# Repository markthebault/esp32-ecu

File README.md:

# ESP32 ECU

A home-solderable ESP32-S3 bench monitor and engine-control development platform. The project combines a compact through-hole carrier, ECU Studio in the browser, ESP-NOW screen telemetry, and a shared C++ fuel/spark core exercised with software engine models.

> **Current status: verified software/bench checkpoint.** Feature expansion is paused. All normal physical engine outputs remain inhibited. This is not yet a complete ECU that can run an engine or replace Speeduino.

[Checkpoint and evidence](docs/bench-checkpoint.md) · [Feature coverage](docs/engine-feature-coverage.md) · [Setup guide](docs/web-configuration.md) · [Latest hardware draft](hardware/a7-boost-interface/README.md) · [Tuning compatibility](tuning/README.md)

*A7 CAD draft, not a photograph or fabrication release. Some components use simplified envelopes or have no body model. The raised ESP32 module, header spacing, inward antenna reservation and enclosure fit remain provisional.*

## What it does today

| Area | Implemented capabilities | Current scope |
| --- | --- | --- |
| Sensor monitoring | Six protected analog inputs plus battery and 5 V rail measurement; linear, lookup-table and NTC conversions, 55 kΩ input-loading compensation and optional ratiometric calibration | Firmware and browser paths implemented; actual electrical behavior still needs measurement |
| Configuration | Persistent sensor profiles and engine tunes, import/export, strict validation, schema migration, stale-revision rejection and storage-fault reporting | Same parser/conversion code on target and host; defaults are uncalibrated |
| Crank and cam | Generic missing-tooth decoder, protected Hall interfaces, sync diagnostics and 720° sequential phase handling with cam-loss cuts | Firmware plus generated 60-2/cam events in simulation; target timing unmeasured |
| Fuel and spark | 1–8 virtual even-fire cylinders; batch/wasted, semi-sequential and sequential strategies; 16 × 16 fuel/spark/lambda maps and individual cylinder trims | Shadow calculations and software-in-the-loop (SIL), with physical outputs inhibited |
| Corrections and control | Cranking, warmup/afterstart, acceleration/deceleration, battery/dead-time/dwell compensation, rev limiting, overrun cut and bounded lambda PI; idle, boost/overboost, flex and secondary-table development | Implemented development paths with configuration and diagnostics; no physical actuator acceptance |
| Debugging | Raw ADC/rail/interlock status, listen-only CAN counters, bounded tooth/timing traces and engine logs, source/age/loss labels, JSON and MSL exports | Host checks pass; physical capture integrity and runtime load remain open |
| Paired screens | Authenticated read-only ESP-NOW sensor/engine telemetry; button or UI pairing, candidate approval and persisted unpair | ECU side implemented; screen firmware and real two-device RF tests remain open |
| Tuning tools | Own012 TunerStudio definition and offline MSQ editing; MegaLogViewer HD opens and plots current MSL files | Actual application/file workflows checked; supported online TunerStudio integration is unresolved |

**Shadow** means the ESP32 calculates proposed commands without driving engine outputs. **SIL** means the native C++ ECU receives synthetic sensor/tooth events and drives virtual outputs into a software plant. Neither establishes physical engine operation. The [full coverage matrix](docs/engine-feature-coverage.md) records the details and evidence for each feature.

## ECU Studio and test screenshots

The same local UI runs on the ESP32 service AP and the desktop simulator. These fresh Chrome captures use **synthetic host data**, with no hardware connected. The calibration curve is an unconfirmed example; the engine settings are illustrative defaults.

| Sensor calibration | Engine configuration and diagnostics |
| --- | --- |
|  |  |
| Signal conversion, input diagnosis and connector guidance | Four-cylinder default profile after a completed virtual run |

| Browser-driven engine test | Screen management |
| --- | --- |
|  |  |
| Actual **Run 12 virtual seconds** action, using the unvalidated reduced-order plant | Pair, approve and remove a synthetic screen; no RF packets transmitted |

[Capture sources, checks and image hashes](docs/images/readme/provenance.json) accompany the images. The requested LED policy is steady green normally, blinking blue while pairing and blinking red for detected problems, with faults taking priority. Browser tests verify the requested states, not physical light output. See [pairing, buttons and telemetry](docs/espnow.md).

## Hardware and revision status

- **Carrier:** 120 × 120 mm, six layers, through-hole assembly with ordinary leaded parts and directly soldered DIP devices. The ESP32 remains pluggable.
- **Selected module:** 44-pin Type-C **ESP32-S3 N16R8**, with 16 MB flash and 8 MB PSRAM. The [supplied listing PDF](hardware/references/esp32-s3-44pin-aliexpress.pdf) is preserved in the repository. Actual module/socket dimensions still need confirmation.
- **Fitted engine capacity:** four injector and four smart-coil command channels. Virtual cylinders 5–8 have no fitted drivers. There is no dumb-coil power stage or raw wideband-sensor controller.
- **Mechanical work:** printable screw-mounted enclosure sources, gasket concept and sealed PAIR/RESET button wiring are retained. Later module, antenna, harness and accessory changes still need physical fit checks.

| Revision | Where to look | Status |
| --- | --- | --- |
| A7 carrier + isolated idle/boost accessories | [Carrier CAD and BOM](hardware/a7-boost-interface/README.md), [shared harness and electrical work](docs/engine-boost-hardware.md) | Latest development draft; boost GPIO allocation remains inactive; no fabrication release |
| A6 flex/RGB and A5 idle work | [A6 layout](docs/engine-a6-layout.md), [idle isolation](docs/engine-idle-isolation.md) | Preserved development drafts with electrical/assembly holds |
| A3 board, manufacturing files and case | [Archived hardware](hardware/a3-compact/), [Gerbers/drills](manufacturing/a3/), [enclosure](enclosure/a3/) | Historical package; do not apply its wiring or fit assumptions to A7 |

## What it does not do

- **Run a physical engine.** The normal images keep engine commands and ARM inhibited. Injector flow/flyback, coil behavior, target timing, watchdog/reset behavior and loaded supply performance remain unqualified.
- **Provide the full Speeduino feature set.** Other OEM trigger decoders, raw VR conditioning, VVT, knock processing, staged injection, launch/flat shift/nitrous, stepper idle and autotune are missing. DBW and OEM CAN/immobilizer integration remain outside the current bench scope.
- **Offer supported online TunerStudio tuning.** The transport and offline file paths exist; online application acceptance is still unresolved. Offline MSQ and MegaLogViewer file compatibility do not prove a physical USB connection.
- **Establish engine-model equivalence or a usable calibration.** Comparisons execute pinned production Speeduino code, but retained reference runs still fail finite-step convergence checks. The plants are uncalibrated research models, and no engine has been tested.
- **Establish vehicle or enclosure qualification.** Physical RF/range, surge/EMI, thermal, current capacity, splash resistance and printed fit remain untested. CAD/ERC/DRC and passing software tests do not establish those properties.

## Work in progress and open items

Feature expansion is **paused at the verified checkpoint**, rather than complete. These are the remaining work areas when development resumes:

| Work area | Remaining work |
| --- | --- |
| Hardware release | Measure the real N16R8/socket/antenna geometry; resolve A7 and accessory electrical, exact-part, harness and enclosure holds before releasing matching fabrication files |
| Bench and HIL testing | Instrument real timing, ADC/supply behavior, interlocks, reset/watchdog recovery, dummy-load outputs and two-device ESP-NOW; then assess physical/environmental limits separately |
| Simulator comparison | Resolve failed reference refinements and matched turbo/map assumptions; preserve causal tests and numerical checks instead of treating a plausible RPM trace as acceptance |
| External tools and screens | Resolve online TunerStudio compatibility and physical USB checks; implement and test a separate screen receiver against the authenticated telemetry protocol |
| Broader ECU coverage | Add missing decoders and control features together with their hardware, UI, configuration, diagnostics and fault tests |

[Engine comparison and remaining convergence failures](docs/engine-shaft-integration.md) · [Current tuning evidence](docs/engine-tuning-application.md) · [Target timing limits](docs/engine-target-timing.md)

## Try the desktop UI or build firmware

The host needs Python 3, a C/C++ compiler and the pinned PlatformIO ESP-IDF package for its cJSON bridge. Follow the [setup guide](docs/web-configuration.md) for dependencies and bench wiring. Use a new output/state directory and a free port:

```sh
# Selected-module bench image. This does not flash a device.
python3 scripts/build_firmware_preserved.py \
  --environment compact_n16r8_web \
  --output .cache/engine/NEW-WEB-BUILD

# Same UI, synthetic measurements, no hardware connection.
python3 tools/web_server.py \
  --port 8765 --state .cache/engine/NEW-PREVIEW/profile.json
```

Open **http://127.0.0.1:8765**. On the actual device, service AP access requires J3 open at startup and a fresh per-boot password read from UART. The [guide](docs/web-configuration.md) covers power isolation and flashing. `compact_n16r8_flex_dev` requires its matching development wiring; `compact_a3_web` belongs to historical A3 hardware.

## What has been verified

The [checkpoint record](reports/engine/bench-checkpoint/README.md) contains the full native ASan/UBSan suite, **99 host/API/config/protocol checks**, sensor-storage fault tests, **four Chrome workflows** and **three fresh inhibited firmware builds**, with source/build hashes and independent review. No device was flashed. For this README, calibration, profile/logging and pairing browser checks were rerun successfully, followed by the captured four-cylinder SIL/UI workflow above.

The verified scope is software and declared bench paths. Physical hardware, RF, fit and engine operation remain open.

<details>
<summary>Historical A3 build package and earlier revisions</summary>

The original deliverables remain available for their original revision:

[Grouped BOM](hardware/a3-compact/BOM.md) · [Shopping CSV](hardware/a3-compact/bom-shopping.csv) · [KiCad project](hardware/a3-compact/esp32-ecu.kicad_pro) · [26-page manual](output/pdf/esp32-ecu-a3-build-calibration-debug-manual.pdf) · [Print files](enclosure/a3/) · [Complete A3 ZIP](build/esp32-ecu-a3-120-web-manual-case.zip)

[A3 native CAD checks](reports/a3/validation-summary.json) and [CAD enclosure-fit report](enclosure/a3/fit-check.json) are historical software/CAD evidence. They do not qualify a printed assembly or later hardware. Exact passive parts and some fit-dependent purchases remain flagged in the BOM.

[Revision history](docs/history.md) · [Original compact-board notes](docs/compact.md)

</details>

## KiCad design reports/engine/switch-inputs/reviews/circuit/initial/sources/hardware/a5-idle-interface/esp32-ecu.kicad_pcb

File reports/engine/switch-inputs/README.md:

# Guarded switch inputs: development checkpoint

Target firmware now acquires the two SW2-J4-DRAFT1 contacts, binds coherent source-tagged samples into the controller, latches faults across skipped control observations and exposes bus/wiring diagnostics in the UI. Defaults make no I2C device requests. Source timestamps, readback/challenge checks, measured acceptance budgets and requalification are explicit. Selected web-build engine outputs remain inhibited.

The separate80x60mm THT accessory has a native schematic/routed PCB, candidate BOM, incompatible internal/contact connectors and a reviewed ground-return pour. **HOLD: no fabrication, physical engine, electrical/environmental, thermal or enclosure-fit qualification.** The expander selftest cannot qualify an analog conditioner or prove two-wire continuity. Fresh secondary-enabled coupled engine acceptance remains open.

- [Current hardware/wiring/debug guide](../../../hardware/switch-inputs/README.md)
- [Source bindings](source-bindings.json), [checks](checks.json) and [artifact manifest](artifact-manifest.json)
- [Independent software assessment](reviews/software/assessment.txt) and [review](reviews/software/review.json):12,278 assertions, including actual engine/switch services, skipped observations, reset/budget/fault races and UI provenance.
- [Independent architecture assessment](reviews/architecture/assessment.txt). The circuit review packet is under `reviews/circuit/`, with its own source bindings, manifest and standalone replay.
- [Native schematic](validation/cad/schematic.svg), [copper](validation/cad/copper.svg), [reference locator](validation/reference-locator/assembly.svg). The locator uses an annotation-only export copy; all serialized non-reference tokens and geometry match the unchanged production PCB. It is not a fit/assembly qualification.
- [Circuit results](validation/circuit/results.json):95 conditional ngspice cases and retained custom decks/vectors. Generic transistor/diode/clamp/supervisor assumptions are not manufacturer models. Bus-feed and carrier3V3-feed currents are separate. Steady18V experiments are not input ratings or automotive surge tests.
- Native/full existing Python tests, three additional stale-binding tests, eight installed-Chrome workflows and three Linux target builds passed. Static output-policy/ISR/USB audits do not establish actual timing, heap, stack or physical behavior.

The immutable software review copied the earlier secondary feature guide as context. The sole declared difference is the updated guide describing this implemented path and its prototype/physical gates; accepted software remains byte-identical. Original local review manifests are retained. Their publication projections explicitly list omitted manufacturer document/page copies and compiled executables/objects. The full local research cache remains intact. The circuit review has a separate standalone publication manifest.

Verification is archival by default. Later project changes do not rewrite this checkpoint. From the repository root:

```sh
python3 tools/verify_switch_inputs_evidence.py
python3 tools/verify_switch_inputs_evidence.py --check-live-sources
uv run --with numpy python tools/verify_switch_inputs_evidence.py --replay --ngspice .cache/tools/ngspice-package/payload/usr/bin/ngspice
```

Replay rebuilds frozen portable/actual-service independent probes in a temporary directory. The optional circuit replay requires the recorded ngspice binary and compares all95 result rows. Native KiCad/target builds and hardware measurements are separate operations. Nothing was flashed and no vendor message was sent.

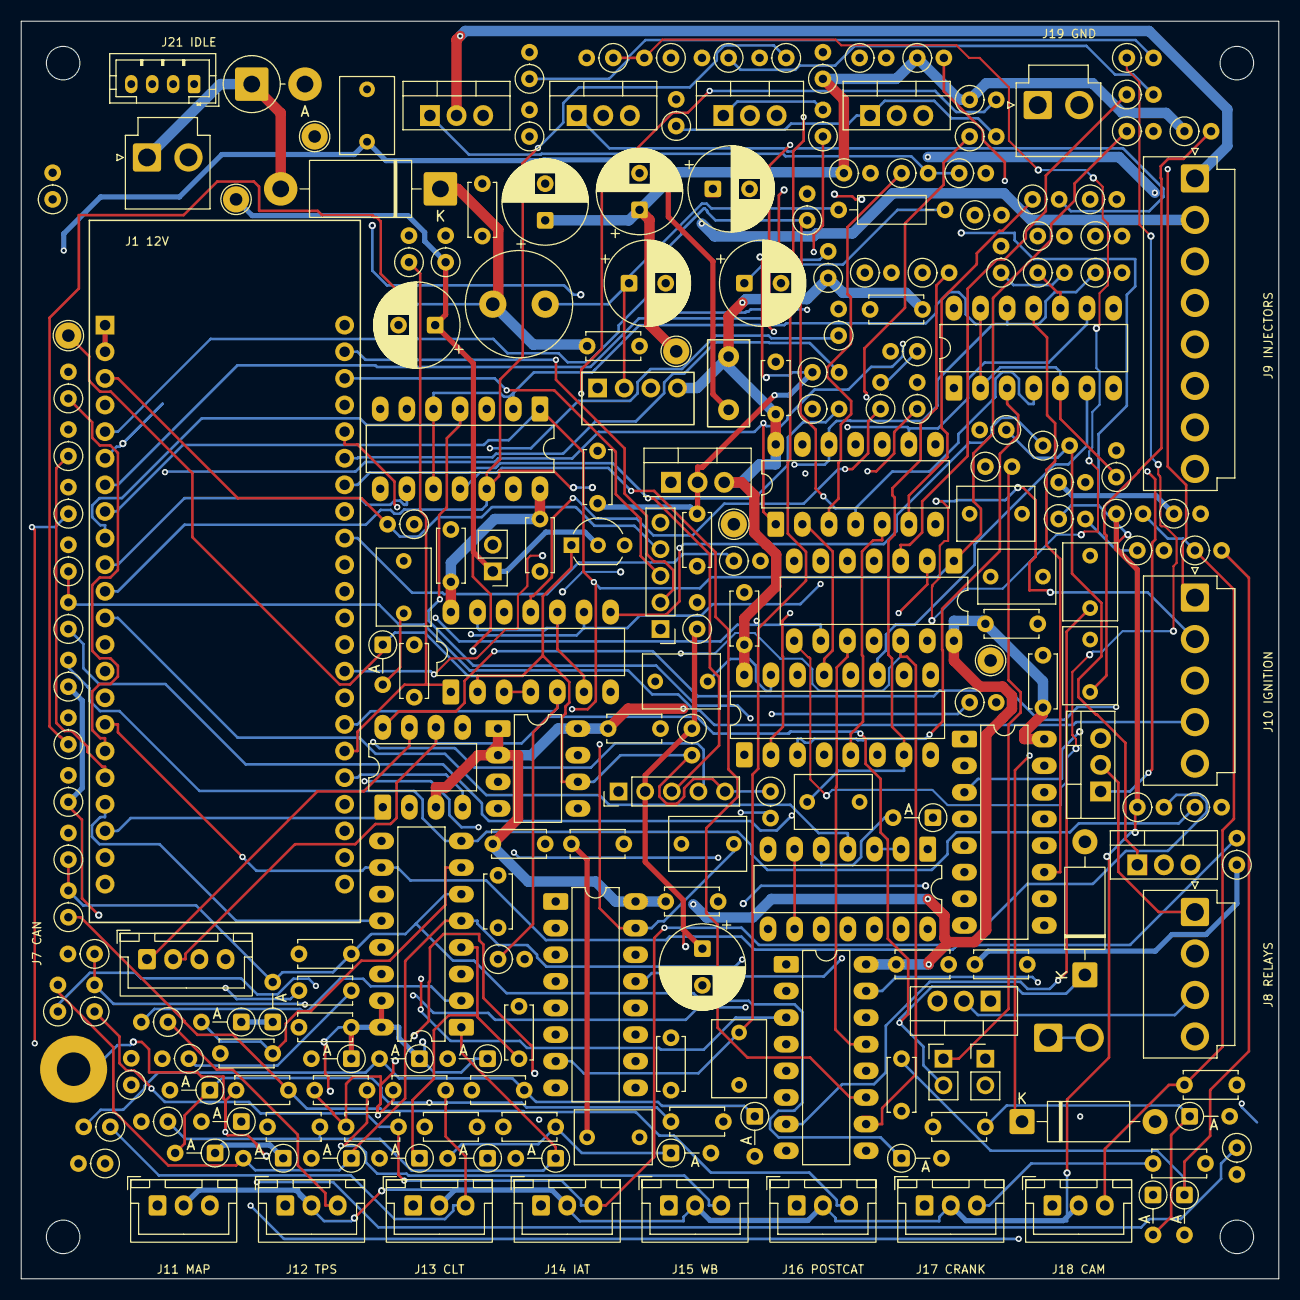
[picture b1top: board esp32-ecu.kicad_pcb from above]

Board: 6 copper layers, 120.0 x 120.0 mm, 221 parts (0 on the bottom side), 119 nets.

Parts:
C1, C2, C45: 47u 63V; CP_Radial_D8.0mm_P3.50mm
C3, C46: 100n 100V; C_Disc_D5.0mm_W2.5mm_P5.00mm
C5, C6: 22u 16V electrolytic; CP_Radial_D8.0mm_P3.50mm
C9: 22u 10V ESR 0.3-1R; CP_Radial_D8.0mm_P3.50mm
C10, C14, C15, C16, C28, C32, C33, C34, C35, C36, C37, C38, C39, C40, C41, C42, C43: 100n; C_Disc_D5.0mm_W2.5mm_P5.00mm
C11, C12, C29: 1u; C_Rect_L7.2mm_W5.0mm_P5.00mm
C13: 10u; CP_Radial_D8.0mm_P3.50mm
C20, C21, C22, C23, C24, C25, C26, C27: 10n; C_Disc_D5.0mm_W2.5mm_P5.00mm
C30, C31: 100p C0G; C_Disc_D5.0mm_W2.5mm_P5.00mm
C47: 4.7n 100V; C_Disc_D5.0mm_W2.5mm_P5.00mm
C61, C62, C63, C64: 270n 5% FILM; C_Rect_L7.2mm_W5.0mm_P5.00mm
C81, C82, C83, C84: 68n 5% FILM; C_Rect_L7.2mm_W5.0mm_P5.00mm
C150, C151, C152, C153, C154, C155: 1n C0G 100V; C_Disc_D5.0mm_W2.5mm_P5.00mm
C156, C157: 100p C0G 100V; C_Disc_D5.0mm_W2.5mm_P5.00mm
D1: 1.5KE27CA; D_DO-201AD_P5.08mm_Vertical_AnodeUp
D2: SB5100; D_DO-201AD_P15.24mm_Horizontal
D3, D100, D101, D110, D111, D120, D121, D130, D131, D140, D141, D150, D151, D160, D161, D170, D171, D200, D201, D210, D211: BAT85; D_DO-35_SOD27_P3.81mm_Vertical_AnodeUp
D22, D23: P6KE24CA; D_DO-15_P12.70mm_Horizontal
F2: PTC 100mA radial; PTC_MF_R010
H1, H2, H3, H4: M3 NPTH; MountingHole_3.2mm_M3
H5: M3 SHIELD LUG; MountingHole_3.2mm_M3_Pad
J1: FUSED_KEY_12V; JST_VH_B2P-VH_1x02_P3.96mm_Vertical
J2: UART_FLASH_3V3_ONLY; PinHeader_1x05_P2.54mm_Vertical
J3: NORMALLY_OPEN_INTERLOCK; PinHeader_1x02_P2.54mm_Vertical
J4: EXPANSION_3V3; PinHeader_1x05_P2.54mm_Vertical
J7: CAN_H_L_G_SHIELD; JST_XH_B4B-XH-A_1x04_P2.50mm_Vertical
J8: EXTERNAL_RELAYS; JST_VH_B4P-VH_1x04_P3.96mm_Vertical
J9: INJECTOR_LOW_SIDES; JST_VH_B8P-VH_1x08_P3.96mm_Vertical
J10: SMART_COIL_5V_LOGIC; JST_VH_B5P-VH_1x05_P3.96mm_Vertical
J11: MAP; JST_XH_B3B-XH-A_1x03_P2.50mm_Vertical
J12: TPS; JST_XH_B3B-XH-A_1x03_P2.50mm_Vertical
J13: CLT; JST_XH_B3B-XH-A_1x03_P2.50mm_Vertical
J14: IAT; JST_XH_B3B-XH-A_1x03_P2.50mm_Vertical
J15: LAMBDA_WB; JST_XH_B3B-XH-A_1x03_P2.50mm_Vertical
J16: POSTCAT_BUF; JST_XH_B3B-XH-A_1x03_P2.50mm_Vertical
J17: CRANK; JST_XH_B3B-XH-A_1x03_P2.50mm_Vertical
J18: CAM; JST_XH_B3B-XH-A_1x03_P2.50mm_Vertical
J19: POWER_RETURN; JST_VH_B2P-VH_1x02_P3.96mm_Vertical
J20: SHIELD_BOND; JST_VH_B2P_SHIELD_Compact
J21: ISOLATED_IDLE_LOGIC; JST_PH_B4B-PH-K_1x04_P2.00mm_Vertical
JP1: CAN_TX_ENABLE_OPEN; PinHeader_1x02_P2.54mm_Vertical
JP2: CAN_TERMINATION_OPEN; PinHeader_1x02_P2.54mm_Vertical
L2: 47uH input filter; L_Radial_D10.0mm_P5.00mm_Fastron_07P
Q1, Q2, Q3, Q4, Q5, Q6, Q7: VNP35N07-E; TO-220-3_Vertical
R7: 100R 0.25W; R_Axial_DIN0207_L6.3mm_D2.5mm_P2.54mm_Vertical
R8, R9, R11, R12, R14, R15, R38, R44, R45, R47, R51, R52, R53, R54, R55, R65, R66, R67, R68, R85, R86, R87, R88, R105, R106, R107, R108, R115, R116, R117, R118: 10k; R_Axial_DIN0207_L6.3mm_D2.5mm_P2.54mm_Vertical
R13, R48, R49, R50, R101, R102, R103, R104: 1k; R_Axial_DIN0207_L6.3mm_D2.5mm_P2.54mm_Vertical
R16, R17: 4.7k; R_Axial_DIN0207_L6.3mm_D2.5mm_P2.54mm_Vertical
R20, R22, R24, R26, R28, R30, R36: 22k 1%; R_Axial_DIN0207_L6.3mm_D2.5mm_P2.54mm_Vertical
R21, R23, R25, R27, R29, R31, R37: 33k 1%; R_Axial_DIN0207_L6.3mm_D2.5mm_P2.54mm_Vertical
R32, R33: 2.49k 1% NTC; R_Axial_DIN0207_L6.3mm_D2.5mm_P2.54mm_Vertical
R34: 120k 1%; R_Axial_DIN0207_L6.3mm_D2.5mm_P2.54mm_Vertical
R35: 10k 1%; R_Axial_DIN0207_L6.3mm_D2.5mm_P2.54mm_Vertical
R40, R42: 33k; R_Axial_DIN0207_L6.3mm_D2.5mm_P2.54mm_Vertical
R41, R43: 2.2k HALL PULLUP; R_Axial_DIN0207_L6.3mm_D2.5mm_P2.54mm_Vertical
R46: 120R; R_Axial_DIN0207_L6.3mm_D2.5mm_P2.54mm_Vertical
R61, R62, R63, R64, R81, R82, R83, R84: 100k 1%; R_Axial_DIN0207_L6.3mm_D2.5mm_P2.54mm_Vertical
R111, R112, R113, R114: 220R; R_Axial_DIN0207_L6.3mm_D2.5mm_P2.54mm_Vertical
R150: 1R 0.5W damping; R_Axial_DIN0207_L6.3mm_D2.5mm_P10.16mm_Horizontal
R151: 1M; R_Axial_DIN0207_L6.3mm_D2.5mm_P2.54mm_Vertical
R152, R153: 47R; R_Axial_DIN0207_L6.3mm_D2.5mm_P2.54mm_Vertical
R154: 2k2 1%; R_Axial_DIN0207_L6.3mm_D2.5mm_P2.54mm_Vertical
TP1: GND; TestPoint_THTPad_D2.5mm_Drill1.2mm
TP2: VIN_PROT; TestPoint_THTPad_D2.5mm_Drill1.2mm
TP3: +5V; TestPoint_THTPad_D2.5mm_Drill1.2mm
TP4: +3V3; TestPoint_THTPad_D2.5mm_Drill1.2mm
TP5: SAFE_N; TestPoint_THTPad_D2.5mm_Drill1.2mm
TP6: RUN_5V; TestPoint_THTPad_D2.5mm_Drill1.2mm
U1: Pololu D36V6F5; Pololu_D36V6F5_vertical
U2: LD1117V33; TO-220-3_Vertical
U3: ESP32-S3 44-pin Type-C N16R8; ESP32_S3_DevKitC_1_socket
U4: MAX1232EPA+; DIP-8_W7.62mm_LongPads
U5: MCP120-315DI/TO; TO-92_Inline_Wide
U6: MCP3208-CI/P; DIP-16_W7.62mm_LongPads
U7: SN74HC14N; DIP-14_W7.62mm_LongPads
U8: MCP2562-E/P; DIP-8_W7.62mm_LongPads
U9, U10, U11, U16, U17: SN74HCT08N; DIP-14_W7.62mm_LongPads
U12, U13, U14, U15: CD74HCT221E; DIP-16_W7.62mm_LongPads

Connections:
+3V3: C9.1, C10.1, C13.1, C14.1, C16.1, C28.1, C29.1, C32.1, C34.1, D101.1, D111.1, D121.1, D131.1, D141.1, D151.1, D161.1, D171.1, D201.1, D211.1, J3.1, J4.2, R7.1, R8.1, R9.1, R11.1, R16.1, R17.1, R38.1, R44.1, R45.1, TP4.1, U2.2, U3.1, U3.2, U5.2, U6.15, U6.16, U7.14, U8.5
+5V: C5.1, C6.1, C15.1, C33.1, C35.1, C36.1, C37.1, C38.1, C39.1, C40.1, C41.1, C42.1, C43.1, F2.1, J21.3, R61.1, R62.1, R63.1, R64.1, R81.1, R82.1, R83.1, R84.1, TP3.1, U1.4, U2.3, U4.1, U4.2, U4.8, U8.3, U9.14, U10.14, U11.14, U12.16, U13.16, U14.16, U15.16, U16.14, U17.14
ADC0: C20.1, D100.1, D101.2, R20.2, R21.1, U6.1
ADC1: C21.1, D110.1, D111.2, R22.2, R23.1, U6.2
ADC2: C22.1, D120.1, D121.2, R24.2, R25.1, U6.3
ADC3: C23.1, D130.1, D131.2, R26.2, R27.1, U6.4
ADC4: C24.1, D140.1, D141.2, R28.2, R29.1, U6.5
ADC5: C25.1, D150.1, D151.2, R30.2, R31.1, U6.6
ADC6: C26.1, D160.1, D161.2, R34.2, R35.1, U6.7
ADC7: C27.1, D170.1, D171.2, R36.2, R37.1, U6.8
ADC_CS: R38.2, U3.16, U6.10
ARM: R15.1, U3.39, U9.1
ARM_SAFE: U9.3, U9.4
BOOT_N: J2.5, R9.2, U3.36
CAM: U3.15, U7.8
CAM_FILT: C31.1, D210.1, D211.2, R42.2, U7.5
CAM_INV: U7.6, U7.9
CAM_RAW: C157.1, J18.3, R42.1, R43.2
CANH: D22.1, J7.1, R46.1, U8.7
CANL: D23.1, J7.2, JP2.2, U8.6
CAN_RX: U3.40, U8.4
CAN_SILENT: JP1.1, R44.2, U8.8
CAN_TERM: JP2.1, R46.2
CAN_TX: R45.2, U3.20, U8.1
CHASSIS: C47.1, C150.2, C151.2, C152.2, C153.2, C154.2, C155.2, C156.2, C157.2, H5.1, J7.4, J20.1, J20.2, R151.1
CLT: C152.1, J13.3, R24.1, R32.2
CRANK: U3.12, U7.4
CRANK_FILT: C30.1, D200.1, D201.2, R40.2, U7.1
CRANK_INV: U7.2, U7.3
CRANK_RAW: C156.1, J17.3, R40.1, R41.2
EN: C12.1, D3.2, J2.4, R8.2, U3.3
FAN_CMD: R55.1, U3.26, U9.12
FAN_GATE: R49.1, U9.11
FAN_IN: Q6.1, R49.2, R52.1
FAN_LS: J8.3, Q6.2
FILTER_DAMP: C45.1, R150.2
GND: C1.2, C2.2, C3.2, C5.2, C6.2, C9.2, C10.2, C11.2, C12.2, C13.2, C14.2, C15.2, C16.2, C20.2, C21.2, C22.2, C23.2, C24.2, C25.2, C26.2, C27.2, C28.2, C29.2, C30.2, C31.2, C32.2, C33.2, C34.2, C35.2, C36.2, C37.2, C38.2, C39.2, C40.2, C41.2, C42.2, C43.2, C45.2, C46.2, C47.2, C61.2, C62.2, C63.2, C64.2, C81.2, C82.2, C83.2, C84.2, D1.2, D22.2, D23.2, D100.2, D110.2, D120.2, D130.2, D140.2, D150.2, D160.2, D170.2, D200.2, D210.2, J1.2, J2.1, J4.1, J7.3, J8.4, J9.5, J9.6, J9.7, J9.8, J10.5, J11.1, J12.1, J13.1, J14.1, J15.1, J16.1, J17.1, J18.1, J19.1, J19.2, J21.4, JP1.2, Q1.3, Q2.3, Q3.3, Q4.3, Q5.3, Q6.3, Q7.3, R7.2, R12.2, R14.2, R15.2, R21.2, R23.2, R25.2, R27.2, R29.2, R31.2, R35.2, R37.2, R47.2, R51.2, R52.2, R53.2, R54.2, R55.2, R65.2, R66.2, R67.2, R68.2, R85.2, R86.2, R87.2, R88.2, R105.2, R106.2, R107.2, R108.2, R115.2, R116.2, R117.2, R118.2, R151.2, R154.2, TP1.1, U1.3, U2.1, U3.22, U3.23, U3.43, U3.44, U4.3, U4.4, U5.3, U6.9, U6.14, U7.7, U7.11, U7.13, U8.2, U9.7, U10.7, U11.7, U12.1, U12.6, U12.8, U12.9, U12.14, U13.1, U13.6, U13.8, U13.9, U13.14, U14.1, U14.6, U14.8, U14.9, U14.14, U15.1, U15.6, U15.8, U15.9, U15.14, U16.7, U17.7
I2C_SCL: J4.4, R17.2, U3.28
I2C_SDA: J4.3, R16.2, U3.29
IAT: C153.1, J14.3, R26.1, R33.2
IDLE_CMD: J21.1, R154.1, U3.13
IGN1_5V: J10.1, R111.2, R115.1
IGN1_CMD: R85.1, U3.8, U11.1, U14.2, U17.1
IGN1_LIMITED: R111.1, U11.3
IGN1_RC: C81.1, R81.2, U14.15
IGN1_RESET_N: U14.3, U17.3
IGN1_WINDOW: U11.2, U14.13
IGN2_5V: J10.2, R112.2, R116.1
IGN2_CMD: R86.1, U3.9, U11.4, U14.10, U17.4
IGN2_LIMITED: R112.1, U11.6
IGN2_RC: C82.1, R82.2, U14.7
IGN2_RESET_N: U14.11, U17.6
IGN2_WINDOW: U11.5, U14.5
IGN3_5V: J10.3, R113.2, R117.1
IGN3_CMD: R87.1, U3.10, U11.9, U15.2, U17.9
IGN3_LIMITED: R113.1, U11.8
IGN3_RC: C83.1, R83.2, U15.15
IGN3_RESET_N: U15.3, U17.8
IGN3_WINDOW: U11.10, U15.13
IGN4_5V: J10.4, R114.2, R118.1
IGN4_CMD: R88.1, U3.11, U11.12, U15.10, U17.12
IGN4_LIMITED: R114.1, U11.11
IGN4_RC: C84.1, R84.2, U15.7
IGN4_RESET_N: U15.11, U17.11
IGN4_WINDOW: U11.13, U15.5
INJ1_CMD: R65.1, U3.4, U10.1, U12.2, U16.1
INJ1_IN: Q1.1, R101.2, R105.1
INJ1_LIMITED: R101.1, U10.3
INJ1_LS: J9.1, Q1.2
INJ1_RC: C61.1, R61.2, U12.15
INJ1_RESET_N: U12.3, U16.3
INJ1_WINDOW: U10.2, U12.13
INJ2_CMD: R66.1, U3.5, U10.4, U12.10, U16.4
INJ2_IN: Q2.1, R102.2, R106.1
INJ2_LIMITED: R102.1, U10.6
INJ2_LS: J9.2, Q2.2
INJ2_RC: C62.1, R62.2, U12.7
INJ2_RESET_N: U12.11, U16.6
INJ2_WINDOW: U10.5, U12.5
INJ3_CMD: R67.1, U3.6, U10.9, U13.2, U16.9
INJ3_IN: Q3.1, R103.2, R107.1
INJ3_LIMITED: R103.1, U10.8
INJ3_LS: J9.3, Q3.2
INJ3_RC: C63.1, R63.2, U13.15
INJ3_RESET_N: U13.3, U16.8
INJ3_WINDOW: U10.10, U13.13
INJ4_CMD: R68.1, U3.7, U10.12, U13.10, U16.12
INJ4_IN: Q4.1, R104.2, R108.1
INJ4_LIMITED: R104.1, U10.11
INJ4_LS: J9.4, Q4.2
INJ4_RC: C64.1, R64.2, U13.7
INJ4_RESET_N: U13.11, U16.11
INJ4_WINDOW: U10.13, U13.5
INTERLOCK: J3.2, R14.1, U3.38, U9.5
LAMBDA_WB: C154.1, J15.3, R28.1
MAIN_IN: Q7.1, R50.2, R53.1
MAIN_LS: J8.1, Q7.2
MAP: C150.1, J11.3, R20.1
POSTCAT_BUF: C155.1, J16.3, R30.1
PUMP_CMD: R54.1, U3.27, U9.9
PUMP_GATE: R48.1, U9.8
PUMP_IN: Q5.1, R48.2, R51.1
PUMP_LS: J8.2, Q5.2
RUN_5V: J21.2, R47.1, R50.1, TP6.1, U9.6, U9.10, U9.13, U16.2, U16.5, U16.10, U16.13, U17.2, U17.5, U17.10, U17.13
SAFE_N: D3.1, J4.5, R11.2, R13.1, TP5.1, U4.6, U5.1, U9.2
SAFE_N_MON: R13.2, U3.30
SENSOR_5V: C11.1, F2.2, J11.2, J12.2, J13.2, J14.2, J15.2, J16.2, J17.2, J18.2, R32.1, R33.1, R36.1, R41.1, R43.1
SPI_CLK: R152.2, U6.13
SPI_CLK_MCU: R152.1, U3.18
SPI_MISO: U3.19, U6.12
SPI_MOSI: R153.2, U6.11
SPI_MOSI_MCU: R153.1, U3.17
TPS: C151.1, J12.3, R22.1
UART_RX: J2.3, U3.25
UART_TX: J2.2, U3.24
VBAT_FUSED: D1.1, D2.2, J1.1
VIN_FILTERED: C2.1, C46.1, L2.2, R150.1, U1.2
VIN_PROT: C1.1, C3.1, D2.1, L2.1, R34.1, TP2.1
WDI: R12.1, U3.31, U4.7
